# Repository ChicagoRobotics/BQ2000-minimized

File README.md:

# BQ2000-minimized
Minimized version of the BQ2000 evaluation module.

I've removed the header pins, and the circuit is designed to charge a pack of 6 NiMH batteries.

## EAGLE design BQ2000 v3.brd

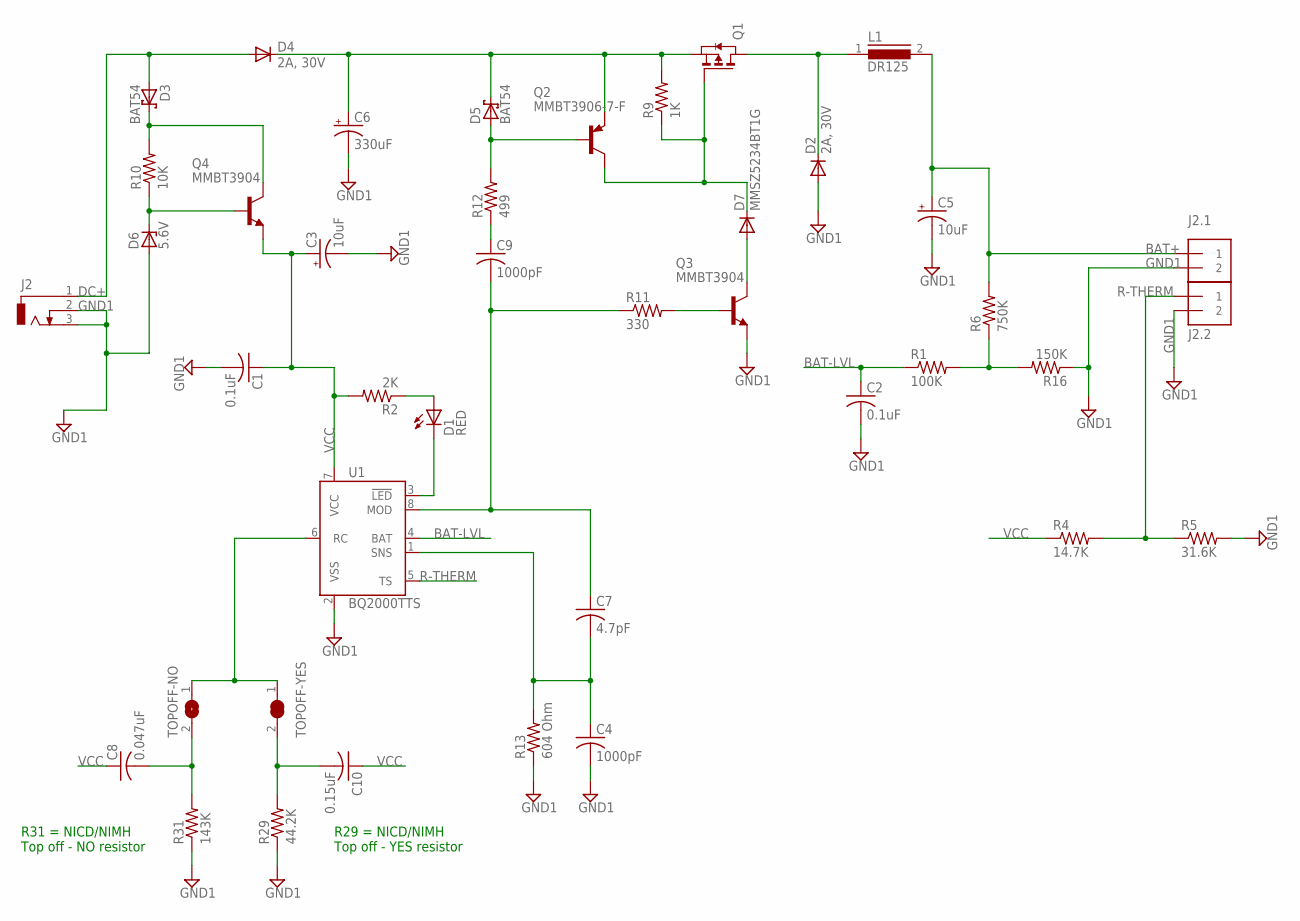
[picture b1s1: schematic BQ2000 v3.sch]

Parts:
C1, C2: 0.1uF; C0603K; MPN C0603C104K5RACTU
C3, C5: 10uF; PANASONIC_C; MPN EEE-FK1E100R
C4, C9: 1000pF; C0603K; MPN C0603C102K5RACTU
C6: 330uF; PANASONIC_E; MPN EEE-FK1E331GP
C7: 4.7pF; C0603K; MPN C0603C479D5GACTU
C8: 0.047uF; C0603K; MPN C0603C473K3RACTU
C10: 0.15uF; C0603K; MPN C0603C154K4RACTU
D1: RED; CHIPLED_0805; MPN AP2012SRCPRV
D2, D4: 2A, 30V; SMB; MPN B230A-13-F
D3, D5: BAT54; SOT23; MPN BAT54
D6: 5.6V; SOT23; MPN BZX84C5V6
D7: MMSZ5234BT1G; SOD123; MPN MMSZ5234BT1G
J2: DCJ0303
J2.1, J2.2: 1X2-3.5MM
L1: DR125; MPN CDRH125NP-101MC
Q1: PMOSSOT23-6; SOT23-6; MPN FDC658AP
Q2: MMBT3906-7-F; SOT23-BEC; MPN MMBT3906-7-F
Q3, Q4: MMBT3904; SOT23-BEC
R1: 100K; R0603; MPN CRCW0603100KFKEA
R2: 2K; R0603; MPN CRCW06032K00FKEA
R4: 14.7K; R0603; MPN CRCW060314K7FKEA
R5: 31.6K; R0603; MPN CRCW060331K6FKEA
R6: 750K; R0603; MPN CRCW0603750KFKEA
R9: 1K; R0603; MPN CRCW06031K00FKEA
R10: 10K; R0603; MPN CRCW060310K0FKEA
R11: 330; R0603; MPN CRCW0603330RFKEA
R12: 499; R0603; MPN CRCW0603499RFKEA
R13: 604 Ohm; R0603; MPN CRCW0603604RFKEA
R16: 150K; R0603
R29: 44.2K; R0603
R31: 143K; R0603
TOPOFF-NO: SOLDERJUMPER_OPEN
TOPOFF-YES: SOLDERJUMPER_CLOSED"; SOLDERJUMPER_CLOSED
U1: BQ2000TTS; TSSOP8; MPN 595-BQ2000PWR

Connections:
BAT+: C5.+, J2.1.1, L1.2, R6.2
BAT-LVL: C2.1, R1.1, U1.4 (BAT)
DC+: D3.1 (A), D4.A, J2.1
GND1: C1.2, C2.2, C3.-, C4.2, C5.-, C6.-, D2.A, D6.1 (A), J2.2, J2.3, J2.1.2, J2.2.2, Q3.E, R5.2, R13.1, R16.1, R29.1, R31.1, U1.2 (VSS)
unnamed: D3.3 (C), Q4.C, R10.2
unnamed: D6.3 (C), Q4.B, R10.1
unnamed: TOPOFF-NO.1, TOPOFF-YES.1, U1.6 (RC)
unnamed: D1.A, R2.1
unnamed: D1.C, U1.3 (!LED)
unnamed: C4.1, C7.2, R13.2, U1.1 (SNS)
unnamed: C7.1, C9.2, R11.1, U1.8 (MOD)
unnamed: R1.2, R6.1, R16.2
unnamed: C6.+, D4.C, D5.3 (C), Q1.4 (S), Q2.E, R9.2
unnamed: D5.1 (A), Q2.B, R12.2
unnamed: C9.1, R12.1
unnamed: Q3.B, R11.2
unnamed: D7.A, Q3.C
unnamed: D7.C, Q1.3 (G), Q2.C, R9.1
unnamed: D2.C, L1.1, Q1.1 (D), Q1.2 (D), Q1.5 (D), Q1.6 (D)
unnamed: C10.2, R29.2, TOPOFF-YES.2
unnamed: C8.2, R31.2, TOPOFF-NO.2
R-THERM: J2.2.1, R4.2, R5.1, U1.5 (TS)
VCC: C1.1, C3.+, C8.1, C10.1, Q4.E, R2.2, R4.1, U1.7 (VCC)

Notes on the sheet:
R29 = NICD/NIMH Top off - YES resistor
R31 = NICD/NIMH Top off - NO resistor

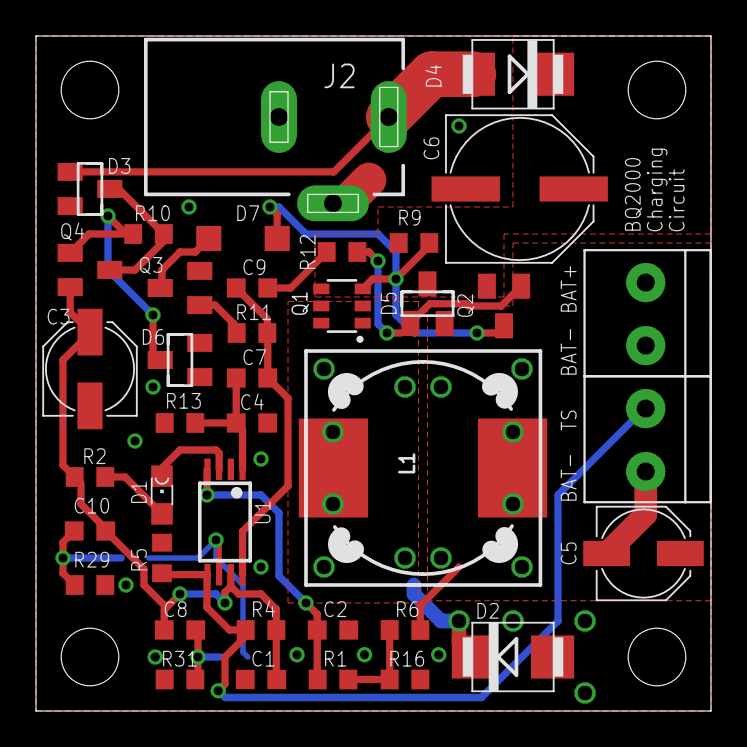
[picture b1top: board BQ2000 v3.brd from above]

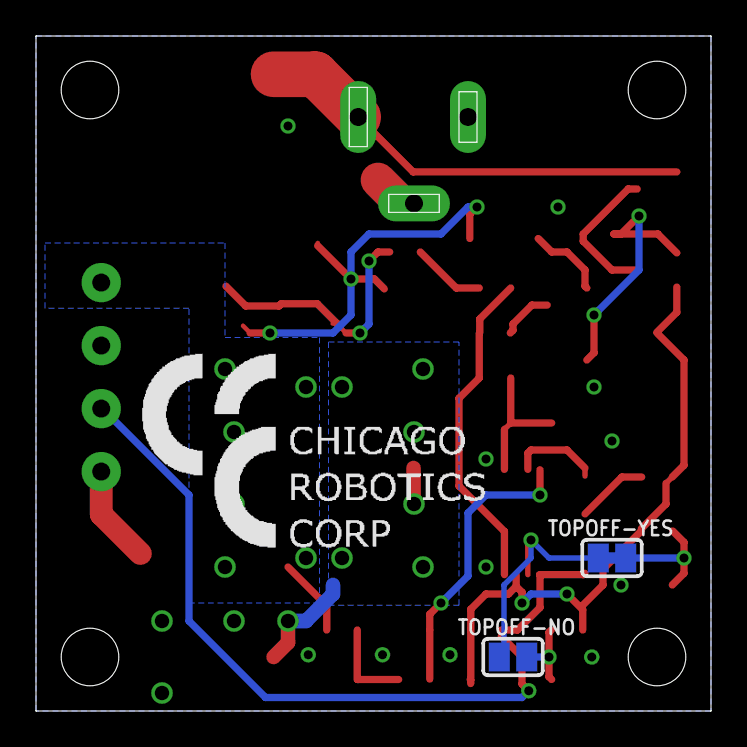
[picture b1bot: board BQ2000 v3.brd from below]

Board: 2 copper layers, 37.5 x 37.5 mm, 42 parts (3 on the bottom side), 23 nets.

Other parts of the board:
U$1: CRC-LOGO

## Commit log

2016-12-13 BQ2000 v3 setup
